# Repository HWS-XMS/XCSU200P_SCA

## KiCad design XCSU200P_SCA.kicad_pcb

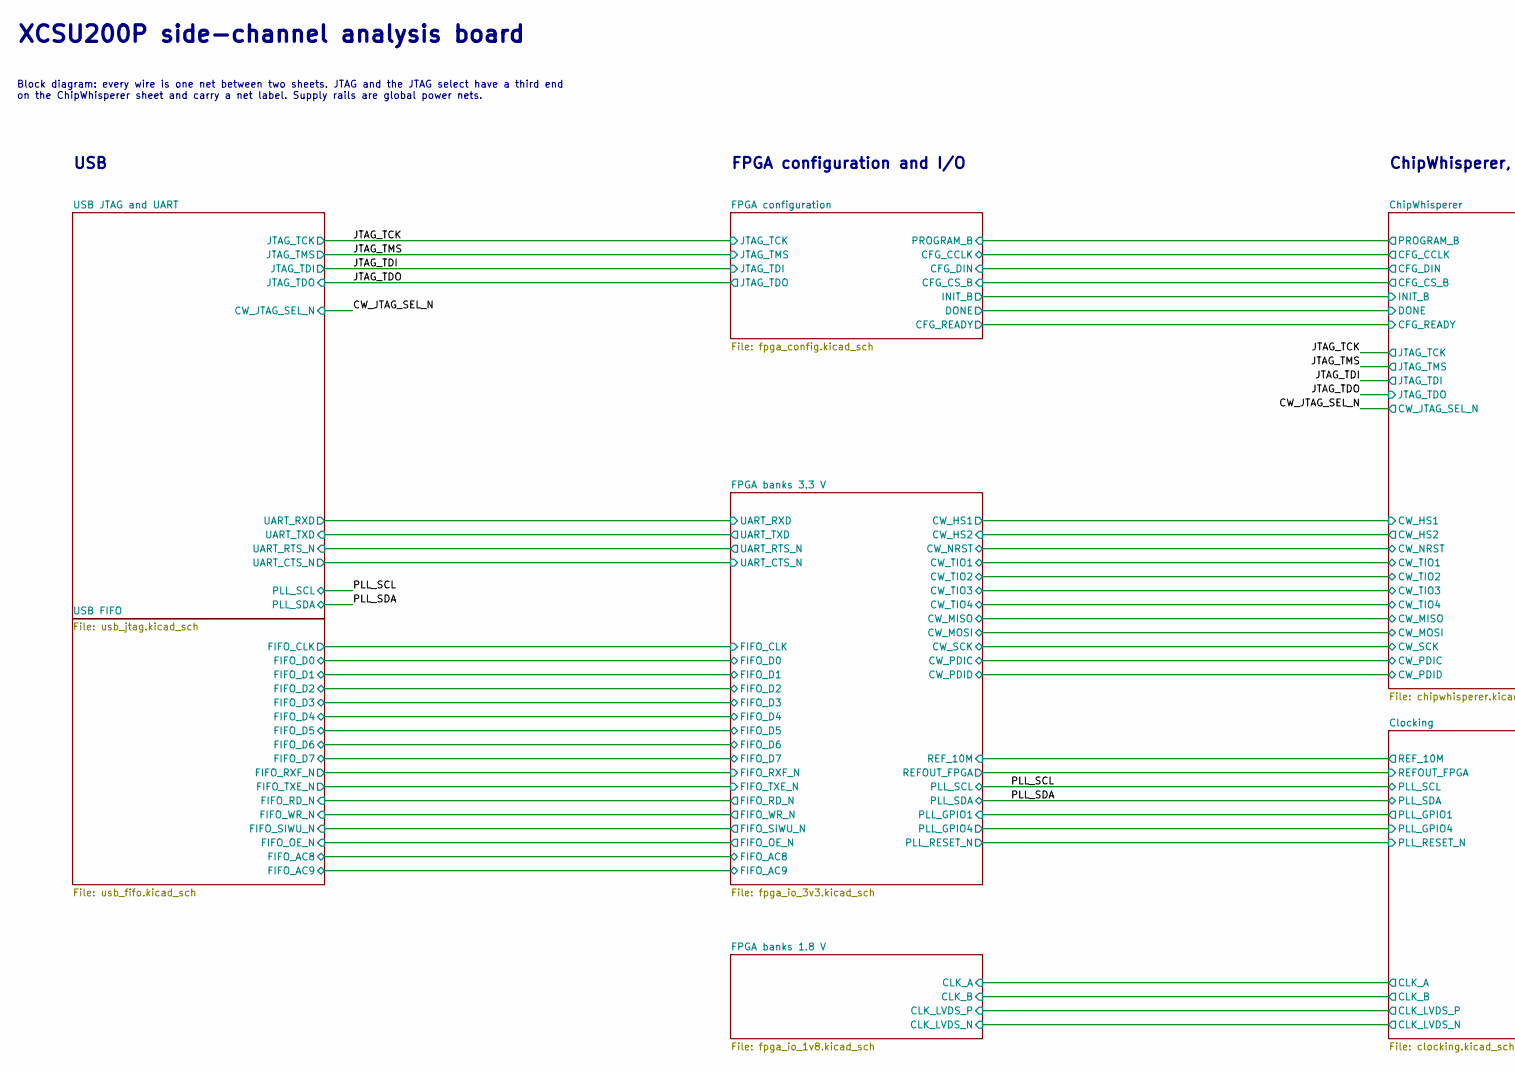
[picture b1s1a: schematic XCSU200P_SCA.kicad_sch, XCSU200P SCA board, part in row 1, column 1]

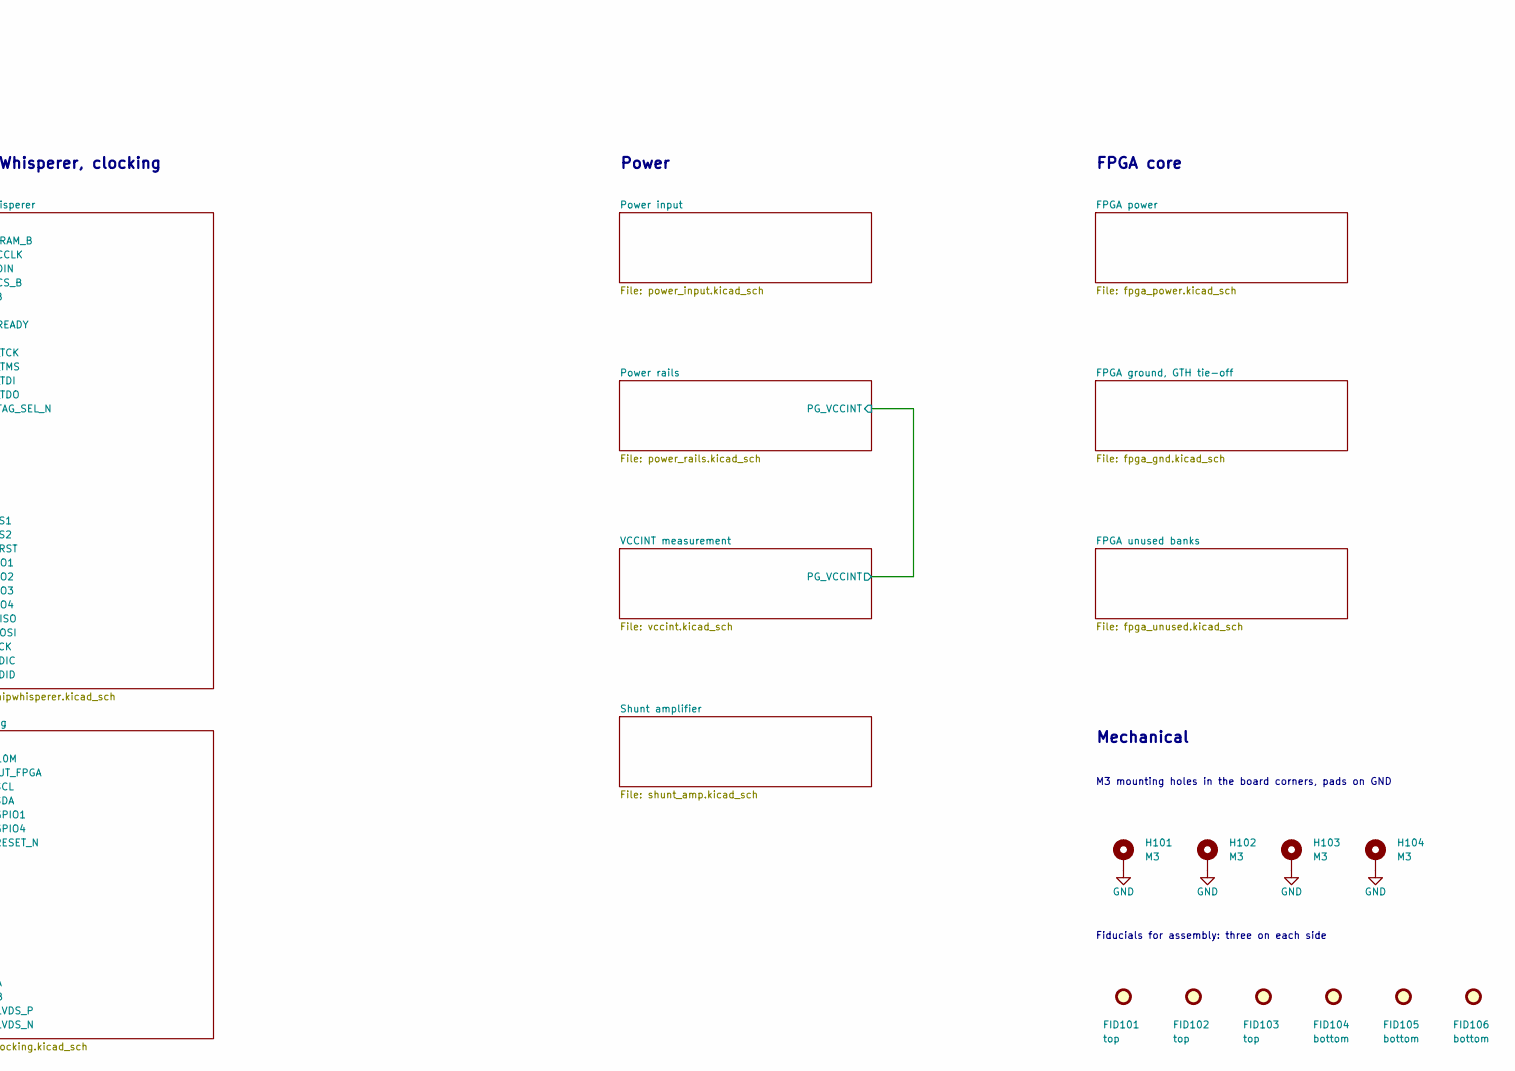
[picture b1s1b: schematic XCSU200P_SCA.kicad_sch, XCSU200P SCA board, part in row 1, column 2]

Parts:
FID101, FID102, FID103: top; Fiducial_1mm_Mask2mm
FID104, FID105, FID106: bottom; Fiducial_1mm_Mask2mm
H101, H102, H103, H104: M3; MountingHole_3.2mm_M3_Pad_Via

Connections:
GND: H101.1 (1_1), H102.1 (1_1), H103.1 (1_1), H104.1 (1_1); also elsewhere on the board

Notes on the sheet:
XCSU200P side-channel analysis board
Block diagram: every wire is one net between two sheets. JTAG and the JTAG select have a third end on the ChipWhisperer sheet and carry a net label. Supply rails are global power nets.
USB
FPGA configuration and I/O
ChipWhisperer, clocking
Power
FPGA core
Mechanical
M3 mounting holes in the board corners, pads on GND
Fiducials for assembly: three on each side

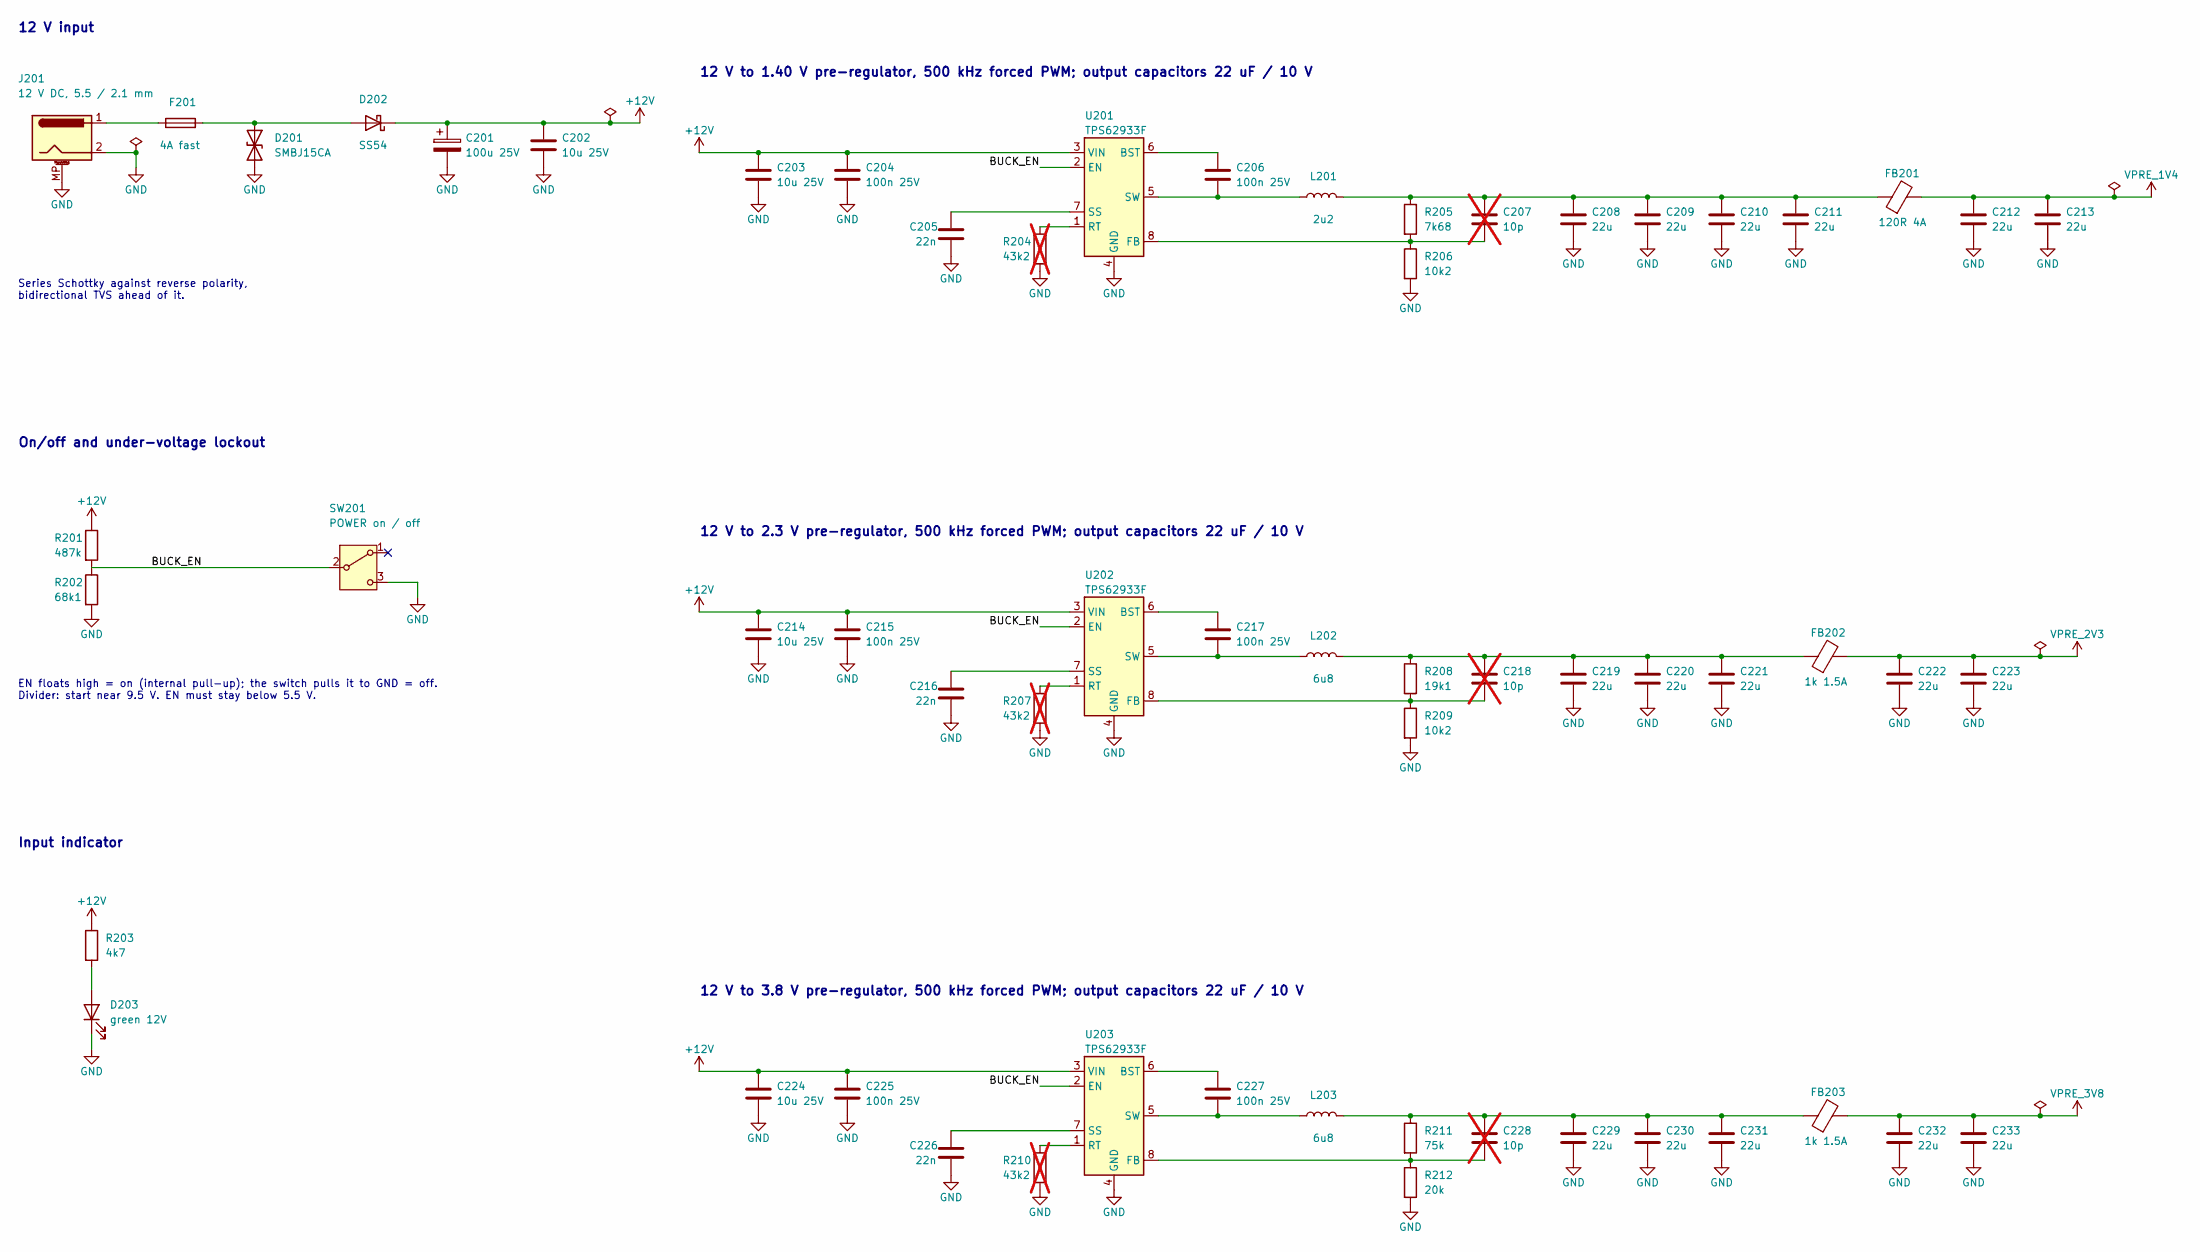
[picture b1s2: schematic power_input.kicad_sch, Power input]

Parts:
C201: 100u 25V; CP_Elec_6.3x7.7; MPN Lelon VES101M1ETR-0607, 6.3 x 7.7 mm; LCSC C176675
C202, C203, C214, C224: 10u 25V; C_1206_3216Metric; MPN Samsung CL31A106KBHNNNE, 50 V X5R; LCSC C13585
C204, C206, C215, C217, C225, C227: 100n 25V; C_0402_1005Metric; MPN Samsung CL05B104KB54PNC, 50 V X7R; LCSC C307331
C205, C216, C226: 22n; C_0402_1005Metric; MPN FH 0402B223K500NT, 50 V X7R; LCSC C1532
C207, C218, C228: 10p; C_0402_1005Metric; MPN Samsung CL05C100JB5NNNC, 50 V C0G; LCSC C32949; not fitted
C208, C209, C210, C211, C212, C213, C219, C220, C221, C222, C223, C229, C230, C231, C232, C233: 22u; C_0805_2012Metric; Rating 10 V; MPN Samsung CL21A226MAQNNNE, 25 V X5R; LCSC C45783
D201: SMBJ15CA; D_SMB; LCSC C211759
D202: SS54; D_SMA; LCSC C22452
D203: green 12V; LED_0603_1608Metric; MPN Lite-On LTST-C191KGKT, 2 V; LCSC C125098
F201: 4A fast; Fuse_1206_3216Metric; LCSC C187596
FB201: 120R 4A; L_0805_2012Metric; LCSC C97001
FB202, FB203: 1k 1.5A; L_0805_2012Metric; LCSC C76817
J201: 12 V DC, 5.5 / 2.1 mm; BarrelJack_CUI_PJ-063AH_Horizontal_Edge; MPN CUI PJ-063AH; LCSC C22434582
L201: 2u2; L_Changjiang_FXL0518; LCSC C475907
L202, L203: 6u8; L_Bourns_SRP5030T; LCSC C1329837
R201: 487k; R_0402_1005Metric; MPN UNI-ROYAL 0402WGF4873TCE; LCSC C27010
R202: 68k1; R_0402_1005Metric; MPN UNI-ROYAL 0402WGF6812TCE; LCSC C11537
R203: 4k7; R_0402_1005Metric; MPN UNI-ROYAL 0402WGF4701TCE; LCSC C25900
R204, R207, R210: 43k2; R_0402_1005Metric; MPN UNI-ROYAL 0402WGF4322TCE; LCSC C25894; not fitted
R205: 7k68; R_0402_1005Metric; MPN UNI-ROYAL 0402WGF7681TCE; LCSC C25919
R206, R209: 10k2; R_0402_1005Metric; MPN UNI-ROYAL 0402WGF1022TCE; LCSC C11660
R208: 19k1; R_0402_1005Metric; MPN UNI-ROYAL 0402WGF1912TCE; LCSC C52036
R211: 75k; R_0402_1005Metric; MPN UNI-ROYAL 0402WGF7502TCE; LCSC C25798
R212: 20k; R_0402_1005Metric; MPN UNI-ROYAL 0402WGF2002TCE; LCSC C25765
SW201: POWER on / off; SW_SPDT_Shouhan_MSK12C02; LCSC C431540
U201, U202, U203: TPS62933F; SOT-583-8; LCSC C5219272

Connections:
+12V: C201.1, C202.1, C203.1, C204.1, C214.1, C215.1, C224.1, C225.1, D202.1 (K), R201.1, R203.1, U201.3 (VIN), U202.3 (VIN), U203.3 (VIN)
/Power input/BUCK_EN: R201.2, R202.1, SW201.2 (B), U201.2 (EN), U202.2 (EN), U203.2 (EN)
GND: C201.2, C202.2, C203.2, C204.2, C205.2, C208.2, C209.2, C210.2, C211.2, C212.2, C213.2, C214.2, C215.2, C216.2, C219.2, C220.2, C221.2, C222.2, C223.2, C224.2, C225.2, C226.2, C229.2, C230.2, C231.2, C232.2, C233.2, D201.2 (A2), D203.1 (K), J201.2, J201.MP (MountPin_MP), R202.2, R204.2, R206.2, R207.2, R209.2, R210.2, R212.2, SW201.3 (C), U201.4 (GND), U202.4 (GND), U203.4 (GND); also elsewhere on the board
unnamed: C207.1, C208.1, C209.1, C210.1, C211.1, FB201.1, L201.2, R205.1
unnamed: C218.1, C219.1, C220.1, C221.1, FB202.1, L202.2, R208.1
unnamed: C228.1, C229.1, C230.1, C231.1, FB203.1, L203.2, R211.1
unnamed: D201.1 (A1), D202.2 (A), F201.2
unnamed: D203.2 (A), R203.2
unnamed: F201.1, J201.1
unnamed: C206.1, U201.6 (BST)
unnamed: C207.2, R205.2, R206.1, U201.8 (FB)
unnamed: R204.1, U201.1 (RT)
unnamed: C205.1, U201.7 (SS)
unnamed: C206.2, L201.1, U201.5 (SW)
unnamed: C217.1, U202.6 (BST)
unnamed: C218.2, R208.2, R209.1, U202.8 (FB)
unnamed: R207.1, U202.1 (RT)
unnamed: C216.1, U202.7 (SS)
unnamed: C217.2, L202.1, U202.5 (SW)
unnamed: C227.1, U203.6 (BST)
unnamed: C228.2, R211.2, R212.1, U203.8 (FB)
unnamed: R210.1, U203.1 (RT)
unnamed: C226.1, U203.7 (SS)
unnamed: C227.2, L203.1, U203.5 (SW)
VPRE_1V4: C212.1, C213.1, FB201.2; also elsewhere on the board
VPRE_2V3: C222.1, C223.1, FB202.2; also elsewhere on the board
VPRE_3V8: C232.1, C233.1, FB203.2; also elsewhere on the board

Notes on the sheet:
12 V input
Series Schottky against reverse polarity, bidirectional TVS ahead of it.
On/off and under-voltage lockout
EN floats high = on (internal pull-up); the switch pulls it to GND = off. Divider: start near 9.5 V. EN must stay below 5.5 V.
Input indicator
12 V to 1.40 V pre-regulator, 500 kHz forced PWM; output capacitors 22 uF / 10 V
12 V to 2.3 V pre-regulator, 500 kHz forced PWM; output capacitors 22 uF / 10 V
12 V to 3.8 V pre-regulator, 500 kHz forced PWM; output capacitors 22 uF / 10 V

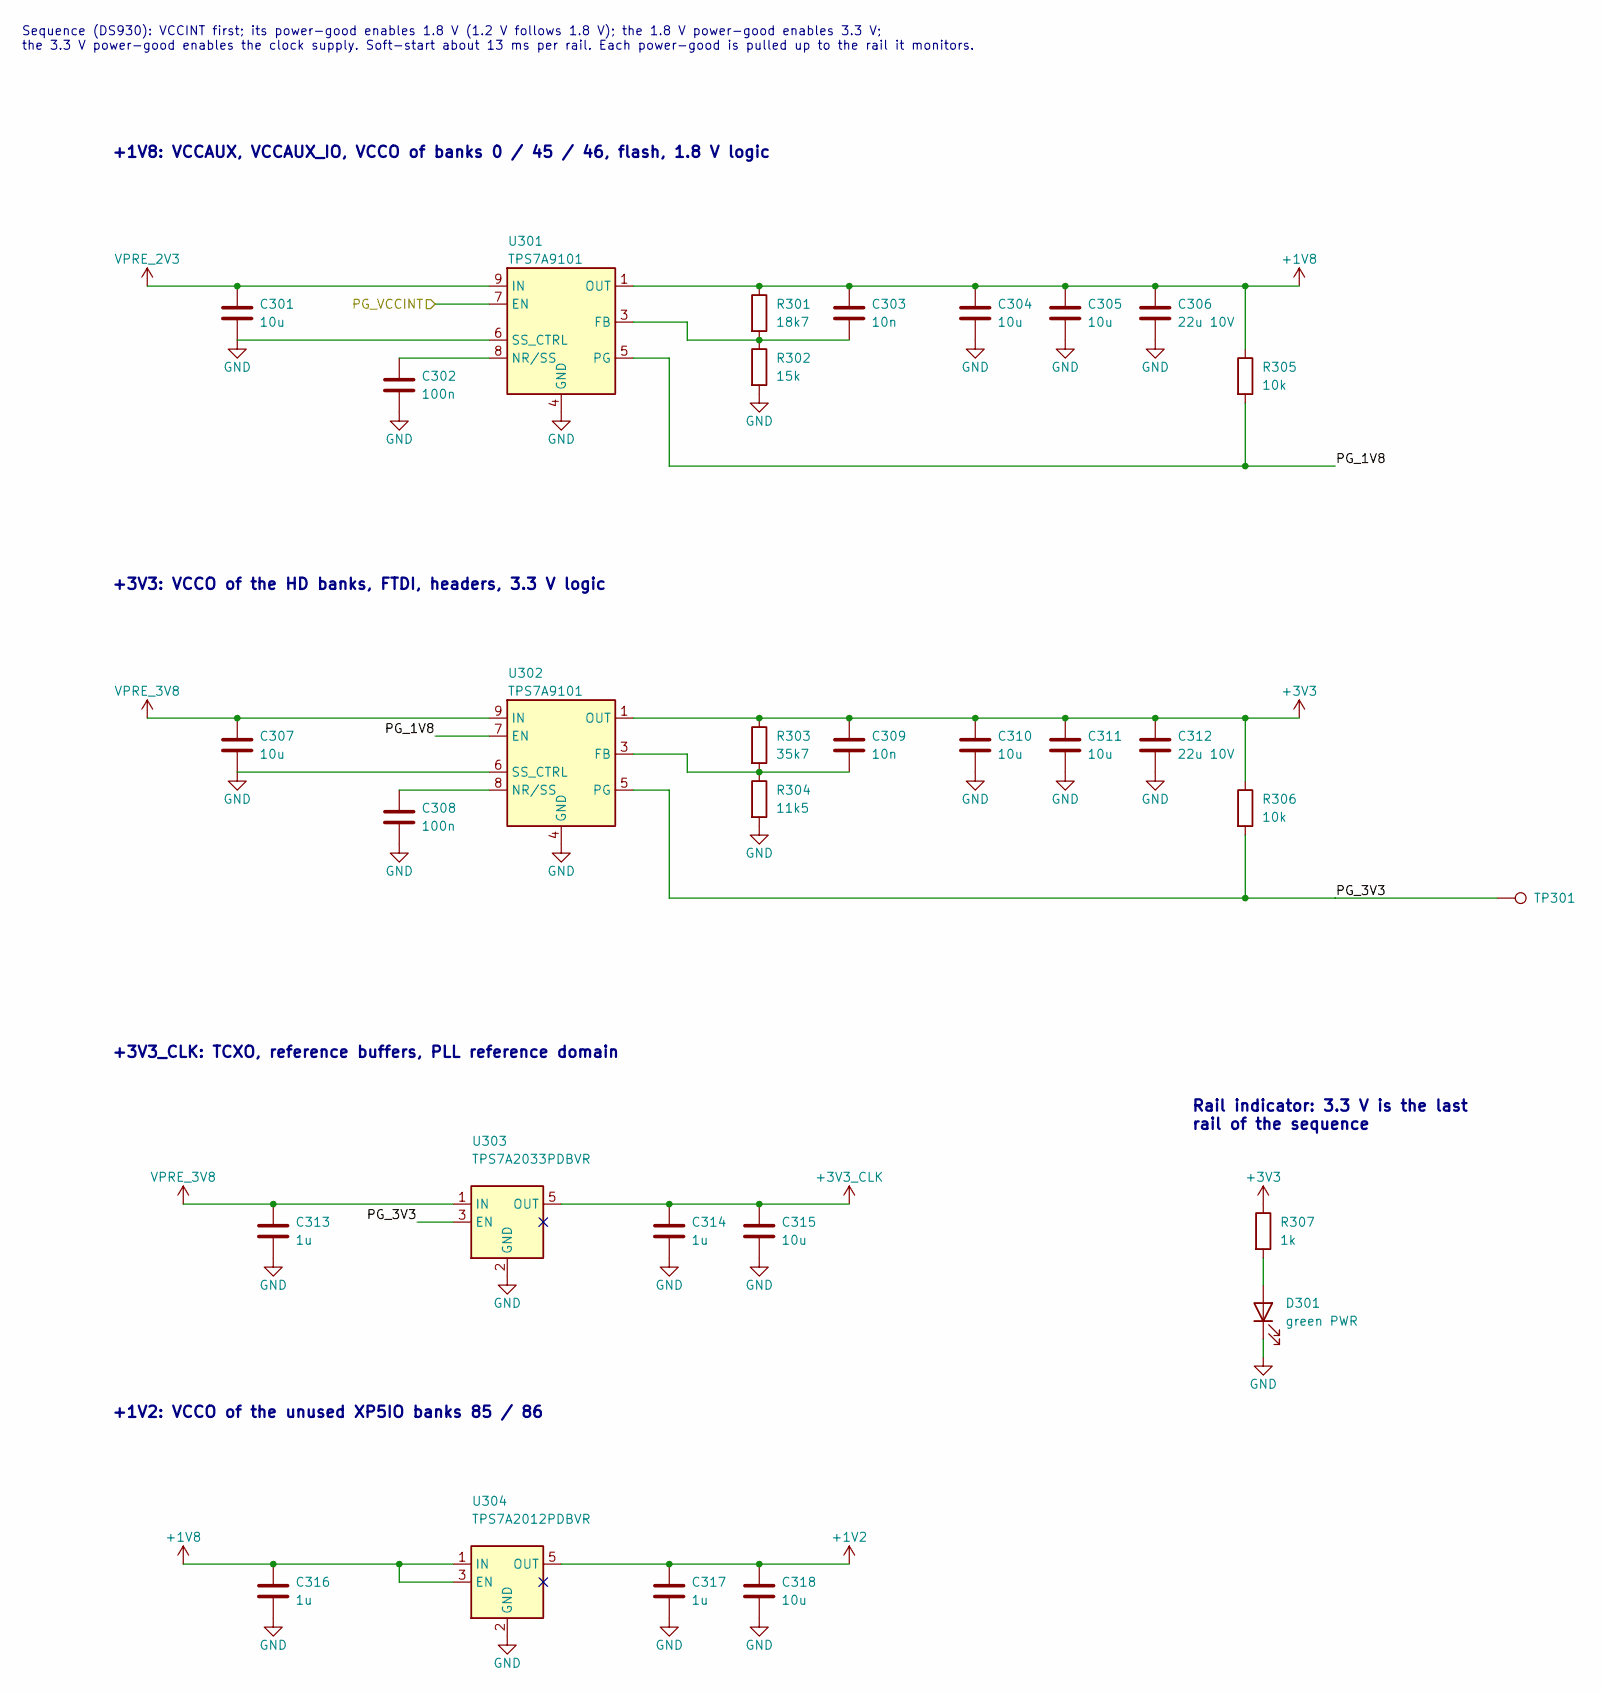
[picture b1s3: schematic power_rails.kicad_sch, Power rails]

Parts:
C301, C304, C305, C307, C310, C311, C315, C318: 10u; C_0603_1608Metric; MPN Samsung CL10A106KP8NNNC, 10 V X5R; LCSC C19702
C302, C308: 100n; C_0402_1005Metric; MPN Samsung CL05B104KO5NNNC, 16 V X7R; LCSC C1525
C303, C309: 10n; C_0402_1005Metric; MPN Samsung CL05B103KB5NNNC, 50 V X7R; LCSC C15195
C306, C312: 22u 10V; C_0805_2012Metric; MPN Samsung CL21A226MAQNNNE, 25 V X5R; LCSC C45783
C313, C314, C316, C317: 1u; C_0402_1005Metric; MPN Samsung CL05A105KA5NQNC, 25 V X5R; LCSC C52923
D301: green PWR; LED_0603_1608Metric; MPN Lite-On LTST-C191KGKT, 2 V; LCSC C125098
R301: 18k7; R_0402_1005Metric; MPN UNI-ROYAL 0402WGF1872TCE; LCSC C11476
R302: 15k; R_0402_1005Metric; MPN UNI-ROYAL 0402WGF1502TCE; LCSC C25756
R303: 35k7; R_0402_1005Metric; MPN UNI-ROYAL 0402WGF3572TCE; LCSC C26975
R304: 11k5; R_0402_1005Metric; MPN UNI-ROYAL 0402WGF1152TCE; LCSC C270653
R305, R306: 10k; R_0402_1005Metric; MPN UNI-ROYAL 0402WGF1002TCE; LCSC C25744
R307: 1k; R_0402_1005Metric; MPN UNI-ROYAL 0402WGF1001TCE; LCSC C11702
TP301: PG_3V3; TestPoint_Pad_D1.0mm
U301, U302: TPS7A9101; Texas_S-PDSO-N10_EP1.2x2mm_ThermalVias; LCSC C2878140
U303: TPS7A2033PDBVR; SOT-23-5; LCSC C2862740
U304: TPS7A2012PDBVR; SOT-23-5; LCSC C2864597

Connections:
+1V2: C317.1, C318.1, U304.5 (OUT); also elsewhere on the board
+1V8: C303.1, C304.1, C305.1, C306.1, C316.1, R301.1, R305.1, U301.1 (OUT), U301.2 (OUT), U304.1 (IN), U304.3 (EN); also elsewhere on the board
+3V3: C309.1, C310.1, C311.1, C312.1, R303.1, R306.1, R307.1, U302.1 (OUT), U302.2 (OUT); also elsewhere on the board
+3V3_CLK: C314.1, C315.1, U303.5 (OUT); also elsewhere on the board
/Power rails/PG_1V8: R305.2, U301.5 (PG), U302.7 (EN)
/Power rails/PG_3V3: R306.2, TP301.1 (1_1), U302.5 (PG), U303.3 (EN)
/Power rails/PG_VCCINT: U301.7 (EN); also elsewhere on the board
GND: C301.2, C302.2, C304.2, C305.2, C306.2, C307.2, C308.2, C310.2, C311.2, C312.2, C313.2, C314.2, C315.2, C316.2, C317.2, C318.2, D301.1 (K), R302.2, R304.2, U301.4 (GND), U301.6 (SS_CTRL), U301.11 (GND), U302.4 (GND), U302.6 (SS_CTRL), U302.11 (GND), U303.2 (GND), U304.2 (GND); also elsewhere on the board
unnamed: D301.2 (A), R307.2
unnamed: C303.2, R301.2, R302.1, U301.3 (FB)
unnamed: C302.1, U301.8 (NR/SS)
unnamed: C309.2, R303.2, R304.1, U302.3 (FB)
unnamed: C308.1, U302.8 (NR/SS)
VPRE_2V3: C301.1, U301.9 (IN), U301.10 (IN); also elsewhere on the board
VPRE_3V8: C307.1, C313.1, U302.9 (IN), U302.10 (IN), U303.1 (IN); also elsewhere on the board

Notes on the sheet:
Sequence (DS930): VCCINT first; its power-good enables 1.8 V (1.2 V follows 1.8 V); the 1.8 V power-good enables 3.3 V; the 3.3 V power-good enables the clock supply. Soft-start about 13 ms per rail. Each power-good is pulled up to the rail it monitors.
+1V8: VCCAUX, VCCAUX_IO, VCCO of banks 0 / 45 / 46, flash, 1.8 V logic
+3V3: VCCO of the HD banks, FTDI, headers, 3.3 V logic
+3V3_CLK: TCXO, reference buffers, PLL reference domain
+1V2: VCCO of the unused XP5IO banks 85 / 86
Rail indicator: 3.3 V is the last rail of the sequence

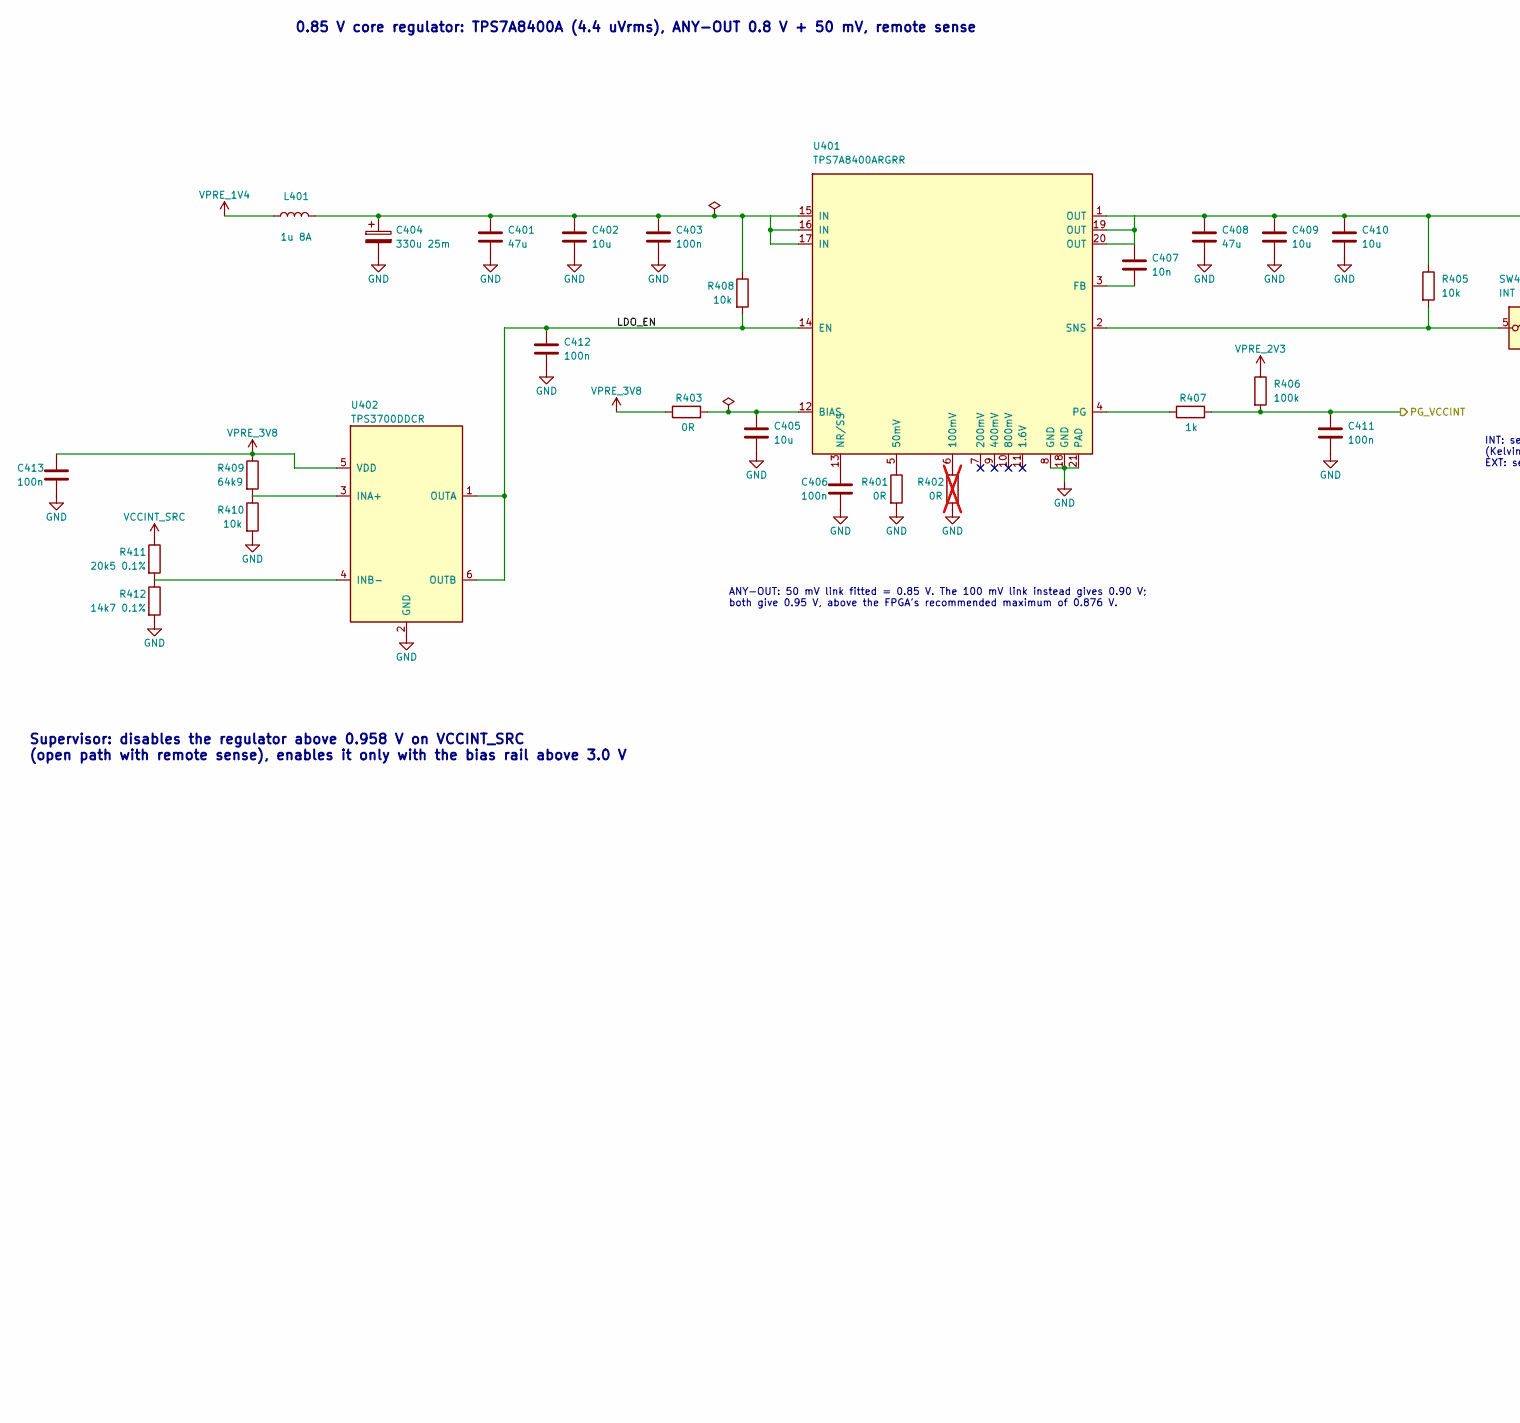
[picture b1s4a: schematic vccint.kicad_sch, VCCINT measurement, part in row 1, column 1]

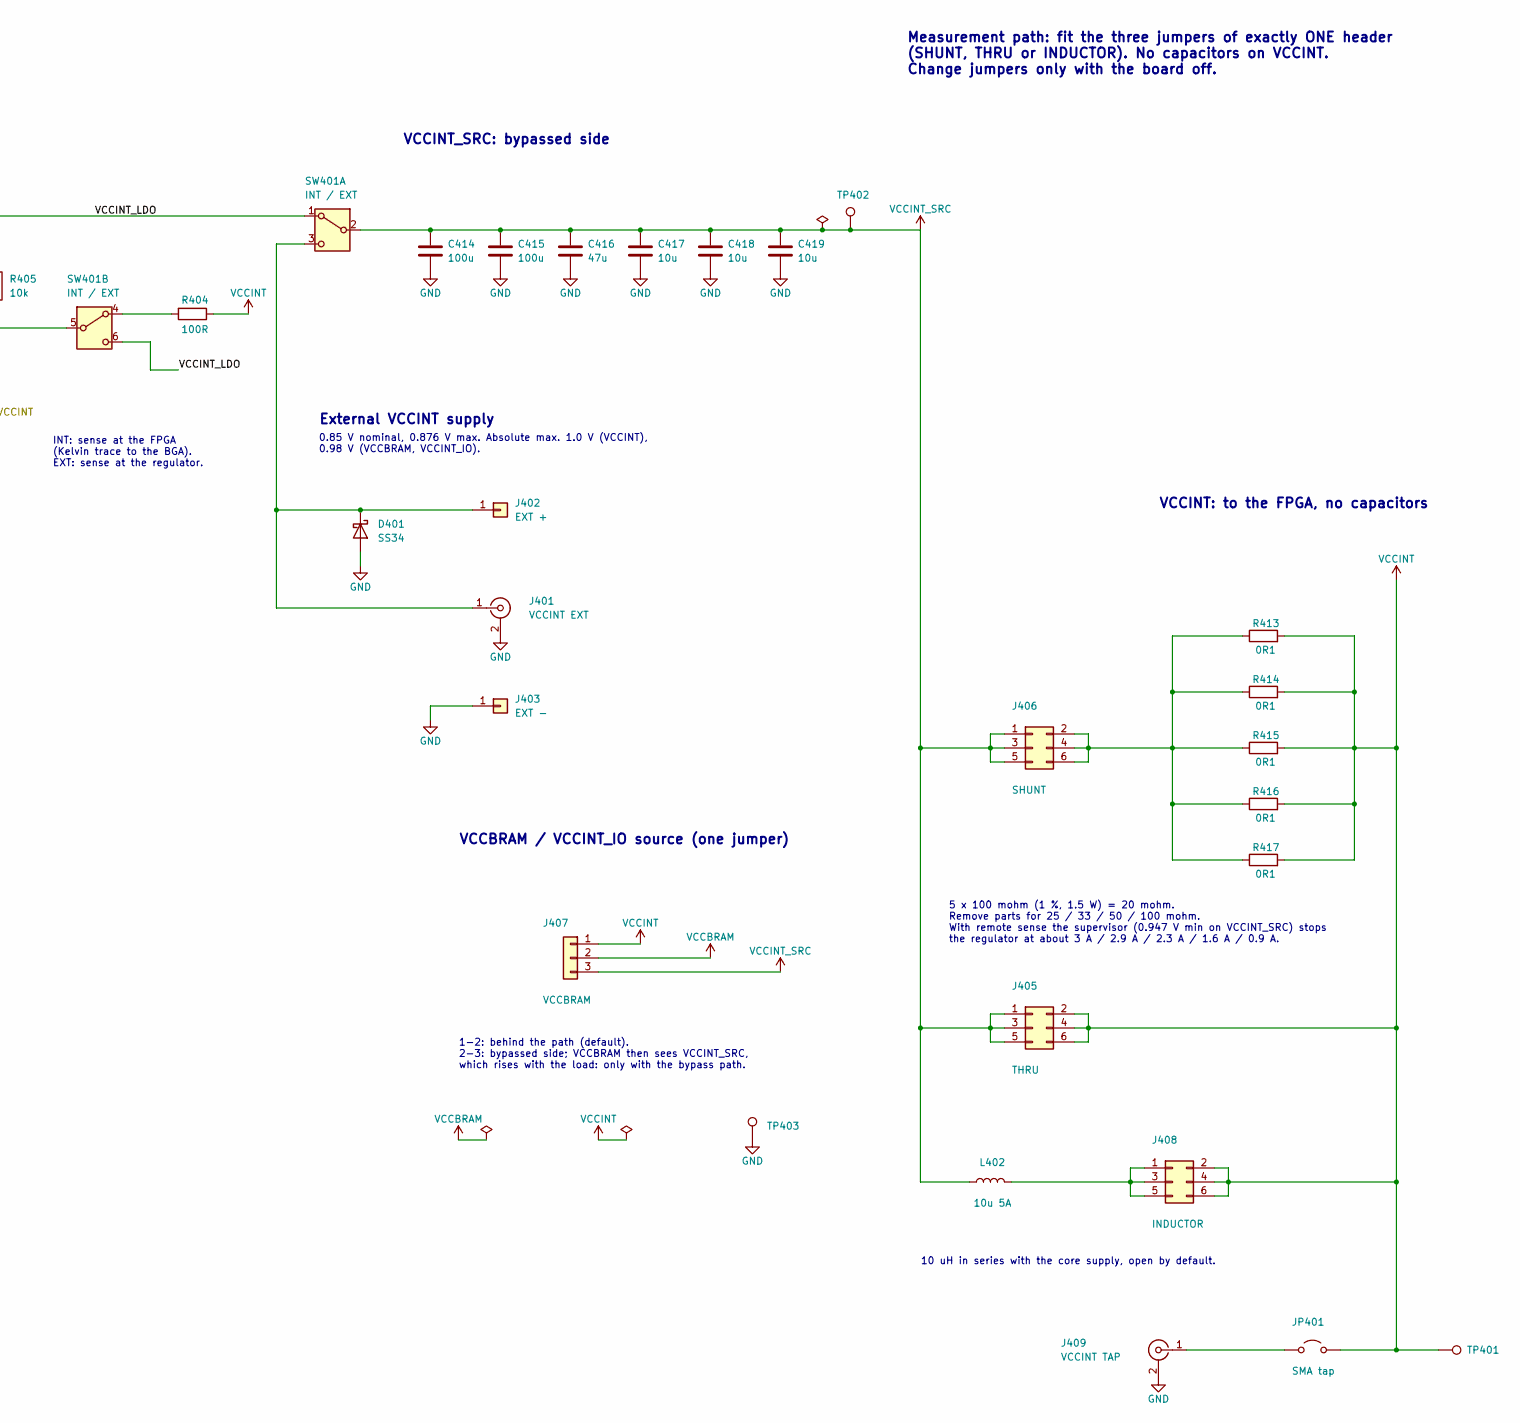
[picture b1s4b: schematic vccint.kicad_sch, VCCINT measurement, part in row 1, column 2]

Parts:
C401, C408, C416: 47u; C_1210_3225Metric; MPN Murata GRM32ER61C476KE15L, 16 V X5R; LCSC C77101
C402, C405, C409, C410, C417, C418, C419: 10u; C_0603_1608Metric; MPN Samsung CL10A106KP8NNNC, 10 V X5R; LCSC C19702
C403, C406, C411, C412, C413: 100n; C_0402_1005Metric; MPN Samsung CL05B104KO5NNNC, 16 V X7R; LCSC C1525
C404: 330u 25m; CP_EIA-7343-20_Kemet-V; MPN Panasonic 6TPE330MAP, 6.3 V; LCSC C79112
C407: 10n; C_0402_1005Metric; MPN Samsung CL05B103KB5NNNC, 50 V X7R; LCSC C15195
C414, C415: 100u; C_1210_3225Metric; MPN Samsung CL32A107MQVNNNE, 6.3 V X5R; LCSC C49066
D401: SS34; D_SMA; LCSC C8678
J401: VCCINT EXT; SMA_Molex_73251-2200_Horizontal_Drill1.6mm; MPN Lian Xin SMA-KWE; LCSC C7498154
J402: EXT +; Banana_Jack_Keystone_575-4_Vertical; MPN Keystone 575-4; LCSC C4944061
J403: EXT -; Banana_Jack_Keystone_575-4_Vertical; MPN Keystone 575-4; LCSC C4944061
J405: THRU; PinHeader_2x03_P2.54mm_Vertical; MPN XFCN PZ254V-12-6P; LCSC C492420
J406: SHUNT; PinHeader_2x03_P2.54mm_Vertical; MPN XFCN PZ254V-12-6P; LCSC C492420
J407: VCCBRAM; PinHeader_1x03_P2.54mm_Vertical; MPN BOOMELE 2.54-1*3P; LCSC C49257
J408: INDUCTOR; PinHeader_2x03_P2.54mm_Vertical; MPN XFCN PZ254V-12-6P; LCSC C492420
J409: VCCINT TAP; SMA_Molex_73251-2200_Horizontal_Drill1.6mm; MPN Lian Xin SMA-KWE; LCSC C7498154
JP401: SMA tap; PinHeader_1x02_P2.54mm_Vertical; MPN XFCN PZ254V-11-02P; LCSC C492401
L401: 1u 8A; L_Changjiang_FXL0518; LCSC C5298209
L402: 10u 5A; L_Sunlord_MWSA0605S; LCSC C408467
R401, R403: 0R; R_0402_1005Metric; MPN UNI-ROYAL 0402WGF0000TCE; LCSC C17168
R402: 0R; R_0402_1005Metric; MPN UNI-ROYAL 0402WGF0000TCE; LCSC C17168; not fitted
R404: 100R; R_0402_1005Metric; MPN UNI-ROYAL 0402WGF1000TCE; LCSC C25076
R405, R408, R410: 10k; R_0402_1005Metric; MPN UNI-ROYAL 0402WGF1002TCE; LCSC C25744
R406: 100k; R_0402_1005Metric; MPN UNI-ROYAL 0402WGF1003TCE; LCSC C25741
R407: 1k; R_0402_1005Metric; MPN UNI-ROYAL 0402WGF1001TCE; LCSC C11702
R409: 64k9; R_0402_1005Metric; MPN UNI-ROYAL 0402WGF6492TCE; LCSC C26984
R411: 20k5 0.1%; R_0402_1005Metric; MPN YAGEO RT0402BRD0720K5L; LCSC C723525
R412: 14k7 0.1%; R_0402_1005Metric; MPN YAGEO RT0402BRD0714K7L; LCSC C281774
R413, R414, R415, R416, R417: 0R1; R_0612_Rohm_LTR18; Rating 1 %, 1.5 W; MPN Rohm LTR18EZPFLR100; LCSC C426512
SW401: INT / EXT; SW_Slide_DPDT_CK_1201M2_E-Switch_500SDP1_P4.70x4.83mm; MPN E-Switch 500SDP1S1M2QEA or C&K 1201M2S3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; LCSC C273377
TP401: VCCINT; TestPoint_Keystone_5005-5009_Compact_NoCircle; MPN Keystone 5005 (red); LCSC C2906763
TP402: VCCINT_SRC; TestPoint_Keystone_5005-5009_Compact_NoCircle; MPN Keystone 5005 (red); LCSC C2906763
TP403: GND; TestPoint_Keystone_5005-5009_Compact_NoCircle; MPN Keystone 5006 (black); LCSC C2906764
U401: TPS7A8400ARGRR; QFN-20-1EP_3.5x3.5mm_P0.5mm_EP2x2mm_ThermalVias; LCSC C524802
U402: TPS3700DDCR; TSOT-23-6; LCSC C33002

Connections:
/Power rails/PG_VCCINT: C411.1, R406.2, R407.2; also elsewhere on the board
/VCCINT measurement/LDO_EN: C412.1, R408.2, U401.14 (EN), U402.1 (OUTA), U402.6 (OUTB)
/VCCINT measurement/VCCINT_LDO: C407.1, C408.1, C409.1, C410.1, R405.1, SW401.1 (A), SW401.6 (C), U401.1 (OUT), U401.19 (OUT), U401.20 (OUT)
GND: C401.2, C402.2, C403.2, C404.2, C405.2, C406.2, C408.2, C409.2, C410.2, C411.2, C412.2, C413.2, C414.2, C415.2, C416.2, C417.2, C418.2, C419.2, D401.2 (A), J401.2 (Ext), J403.1 (Pin_1_1), J409.2 (Ext), R401.2, R402.2, R410.2, R412.2, TP403.1 (1_1), U401.8 (GND), U401.18 (GND), U401.21 (PAD), U402.2 (GND); also elsewhere on the board
unnamed: C401.1, C402.1, C403.1, C404.1, L401.2, R408.1, U401.15 (IN), U401.16 (IN), U401.17 (IN)
unnamed: D401.1 (K), J401.1 (In), J402.1 (Pin_1_1), SW401.3 (C)
unnamed: J406.2, J406.4, J406.6, R413.1, R414.1, R415.1, R416.1, R417.1
unnamed: J408.1, J408.3, J408.5, L402.2
unnamed: J409.1 (In), JP401.2 (B)
unnamed: R404.2, SW401.4 (A)
unnamed: R405.2, SW401.5 (B), U401.2 (SNS)
unnamed: R401.1, U401.5 (50mV)
unnamed: R402.1, U401.6 (100mV)
unnamed: C405.1, R403.2, U401.12 (BIAS)
unnamed: C407.2, U401.3 (FB)
unnamed: C406.1, U401.13 (NR/SS)
unnamed: R407.1, U401.4 (PG)
unnamed: R409.2, R410.1, U402.3 (INA+)
unnamed: R411.2, R412.1, U402.4 (INB-)
VCCBRAM: J407.2; also elsewhere on the board
VCCINT: J405.2, J405.4, J405.6, J407.1, J408.2, J408.4, J408.6, JP401.1 (A), R404.1, R413.2, R414.2, R415.2, R416.2, R417.2, TP401.1 (1_1); also elsewhere on the board
VCCINT_SRC: C414.1, C415.1, C416.1, C417.1, C418.1, C419.1, J405.1, J405.3, J405.5, J406.1, J406.3, J406.5, J407.3, L402.1, R411.1, SW401.2 (B), TP402.1 (1_1)
VPRE_1V4: L401.1; also elsewhere on the board
VPRE_2V3: R406.1; also elsewhere on the board
VPRE_3V8: C413.1, R403.1, R409.1, U402.5 (VDD); also elsewhere on the board

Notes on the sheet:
0.85 V core regulator: TPS7A8400A (4.4 uVrms), ANY-OUT 0.8 V + 50 mV, remote sense
ANY-OUT: 50 mV link fitted = 0.85 V. The 100 mV link instead gives 0.90 V; both give 0.95 V, above the FPGA's recommended maximum of 0.876 V.
INT: sense at the FPGA (Kelvin trace to the BGA). EXT: sense at the regulator.
Supervisor: disables the regulator above 0.958 V on VCCINT_SRC (open path with remote sense), enables it only with the bias rail above 3.0 V
External VCCINT supply
0.85 V nominal, 0.876 V max. Absolute max. 1.0 V (VCCINT), 0.98 V (VCCBRAM, VCCINT_IO).
VCCINT_SRC: bypassed side
Measurement path: fit the three jumpers of exactly ONE header (SHUNT, THRU or INDUCTOR). No capacitors on VCCINT. Change jumpers only with the board off.
5 x 100 mohm (1 %, 1.5 W) = 20 mohm. Remove parts for 25 / 33 / 50 / 100 mohm. With remote sense the supervisor (0.947 V min on VCCINT_SRC) stops the regulator at about 3 A / 2.9 A / 2.3 A / 1.6 A / 0.9 A.
10 uH in series with the core supply, open by default.
VCCINT: to the FPGA, no capacitors
VCCBRAM / VCCINT_IO source (one jumper)
1-2: behind the path (default). 2-3: bypassed side; VCCBRAM then sees VCCINT_SRC, which rises with the load: only with the bypass path.
